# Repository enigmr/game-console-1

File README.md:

## Game Console Project 1

Hobby handheld game console from scratch.

## Top View

## Insides

## Features

- Display: 4.3", 480x272, 16:9, 1200cd/m2, non-touch
- Processor: STM32N657X0
  - Arm Cortex-M55 @ 800 MHz
  - 2D GPU with scaling, rotating, alpha blending, texture mapping
- RAM:
  - 4.2MB on-chip SRAM
  - 32MB off-chip PSRAM
- Storage:
  - 32MB SLC NOR flash
  - Micro SD card slot
- Audio:
  - Stereo DAC with Class-D amplifiers
  - Stereo 1W speakers
- Haptics:
  - Dual vibration motors
- Input:
  - IMU (accelerometer and gyroscope)
  - D-pad
  - A / B / X / Y buttons
  - Start / Select buttons
- Battery:
  - 500mAh Li-Po battery
- Connectivity:
  - USB-C for charging and accessing storage
  - Wi-Fi and Bluetooth via STM32-C6
- Mechanicals:
  - Machined plastic (material TBD)
- Software:
  - Zephyr RTOS
  - Old game console emulators

## Development Tooling

- Schematics and PCB design: KiCad
- 3D modeling: Fusion 360

## Hardware Block Design

TODO

## PCBs

### Top

### Top Bottom

## Schematics 

### Top Sheet

### Audio

### ESP32

### Flash

### Haptics

### IMU

### LCD

### MCU

### Micro SD

### Power

### RAM

### USB Switch

### USB

### Controllers

### Left Board

### Right Board

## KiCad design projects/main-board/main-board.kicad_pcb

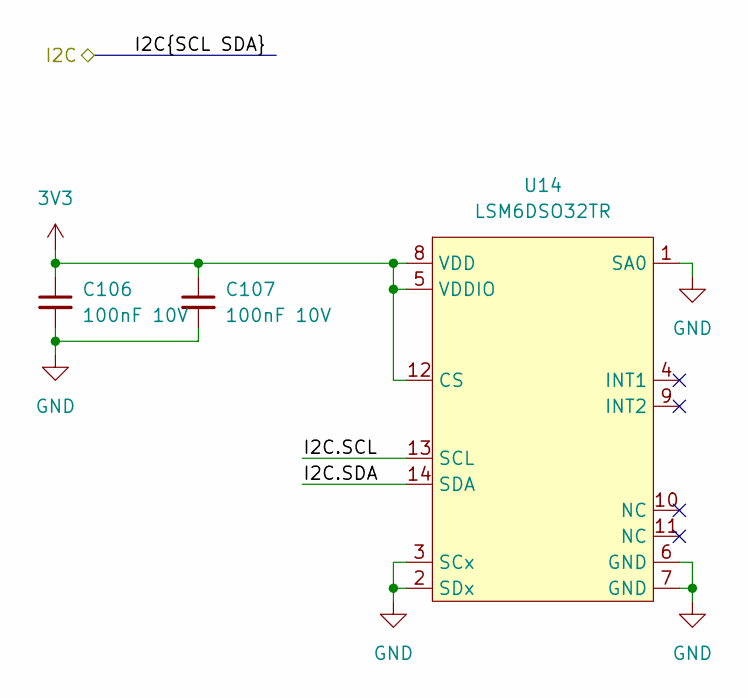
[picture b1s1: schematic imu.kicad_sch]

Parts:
C106, C107: 100nF 10V; C_0402_1005Metric
U14: LSM6DSO32TR

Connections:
3V3: C106.1, C107.1, U14.5 (VDDIO), U14.8 (VDD), U14.12 (CS); also elsewhere on the board
/Audio/I2C.SCL: U14.13 (SCL); also elsewhere on the board
/Audio/I2C.SDA: U14.14 (SDA); also elsewhere on the board
GND: C106.2, C107.2, U14.1 (SA0), U14.2 (SDx), U14.3 (SCx), U14.6 (GND), U14.7 (GND); also elsewhere on the board

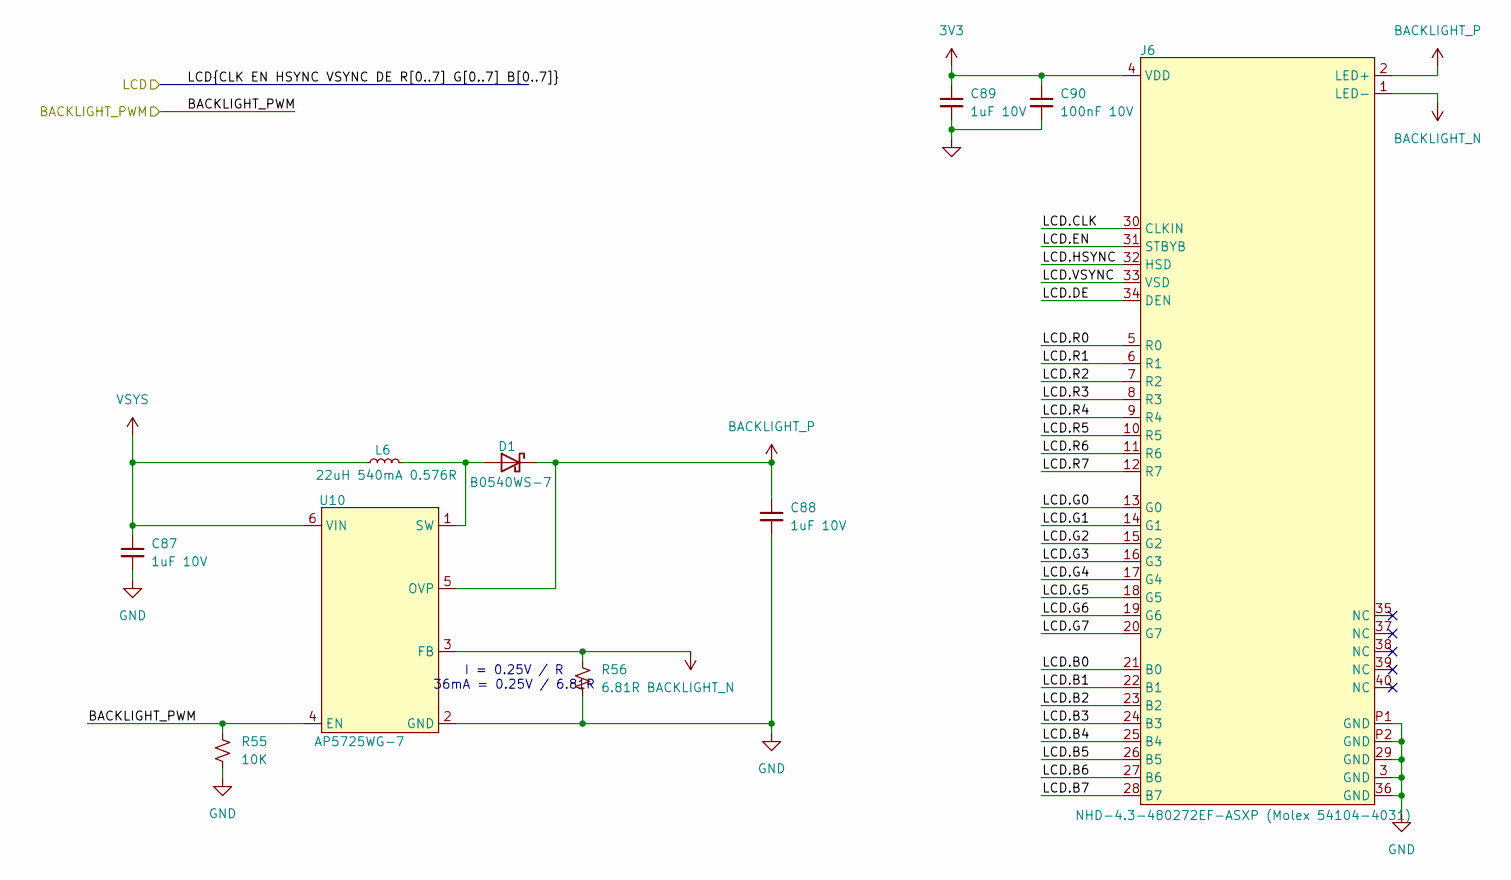
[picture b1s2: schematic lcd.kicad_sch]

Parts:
C87, C88, C89: 1uF 10V; C_0402_1005Metric
C90: 100nF 10V; C_0402_1005Metric
D1: B0540WS-7; SOD323_DIO
J6: NHD-4.3-480272EF-ASXP (Molex 54104-4031); Molex 54104-4031
L6: 22uH 540mA 0.576R; NR4012T220M
R55: 10K; R_0402_1005Metric
R56: 6.81R; R_0402_1005Metric
U10: AP5725WG-7

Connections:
3V3: C89.1, C90.1, J6.4 (VDD); also elsewhere on the board
/LCD/BACKLIGHT_PWM: R55.1, U10.4 (EN); also elsewhere on the board
/LCD/LCD.B0: J6.21 (B0); also elsewhere on the board
/LCD/LCD.B1: J6.22 (B1); also elsewhere on the board
/LCD/LCD.B2: J6.23 (B2); also elsewhere on the board
/LCD/LCD.B3: J6.24 (B3); also elsewhere on the board
/LCD/LCD.B4: J6.25 (B4); also elsewhere on the board
/LCD/LCD.B5: J6.26 (B5); also elsewhere on the board
/LCD/LCD.B6: J6.27 (B6); also elsewhere on the board
/LCD/LCD.B7: J6.28 (B7); also elsewhere on the board
/LCD/LCD.CLK: J6.30 (CLKIN); also elsewhere on the board
/LCD/LCD.DE: J6.34 (DEN); also elsewhere on the board
/LCD/LCD.EN: J6.31 (STBYB); also elsewhere on the board
/LCD/LCD.G0: J6.13 (G0); also elsewhere on the board
/LCD/LCD.G1: J6.14 (G1); also elsewhere on the board
/LCD/LCD.G2: J6.15 (G2); also elsewhere on the board
/LCD/LCD.G3: J6.16 (G3); also elsewhere on the board
/LCD/LCD.G4: J6.17 (G4); also elsewhere on the board
/LCD/LCD.G5: J6.18 (G5); also elsewhere on the board
/LCD/LCD.G6: J6.19 (G6); also elsewhere on the board
/LCD/LCD.G7: J6.20 (G7); also elsewhere on the board
/LCD/LCD.HSYNC: J6.32 (HSD); also elsewhere on the board
/LCD/LCD.R0: J6.5 (R0); also elsewhere on the board
/LCD/LCD.R1: J6.6 (R1); also elsewhere on the board
/LCD/LCD.R2: J6.7 (R2); also elsewhere on the board
/LCD/LCD.R3: J6.8 (R3); also elsewhere on the board
/LCD/LCD.R4: J6.9 (R4); also elsewhere on the board
/LCD/LCD.R5: J6.10 (R5); also elsewhere on the board
/LCD/LCD.R6: J6.11 (R6); also elsewhere on the board
/LCD/LCD.R7: J6.12 (R7); also elsewhere on the board
/LCD/LCD.VSYNC: J6.33 (VSD); also elsewhere on the board
BACKLIGHT_N: J6.1 (LED-), R56.1, U10.3 (FB)
BACKLIGHT_P: C88.1, D1.1 (K), J6.2 (LED+), U10.5 (OVP)
GND: C87.2, C88.2, C89.2, C90.2, J6.3 (GND), J6.29 (GND), J6.36 (GND), J6.P1 (GND), J6.P2 (GND), R55.2, R56.2, U10.2 (GND); also elsewhere on the board
unnamed: D1.2 (A), L6.2, U10.1 (SW)
VSYS: C87.1, L6.1, U10.6 (VIN); also elsewhere on the board

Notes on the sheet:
I = 0.25V / R 36mA = 0.25V / 6.81R

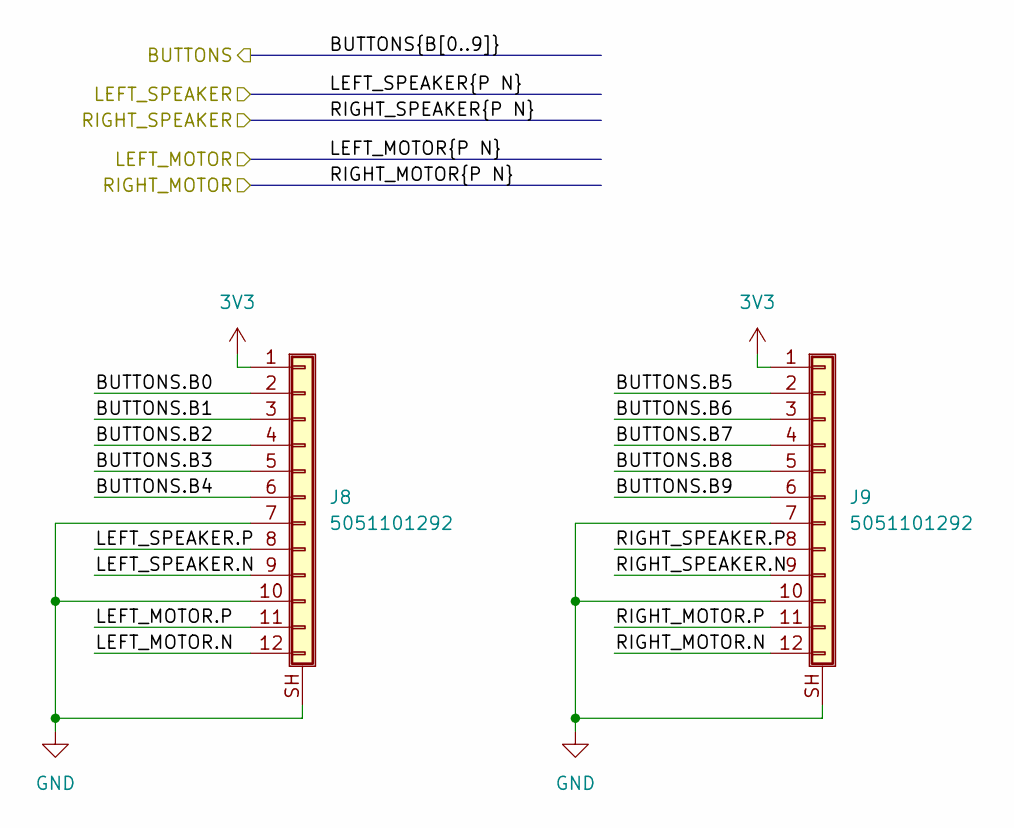
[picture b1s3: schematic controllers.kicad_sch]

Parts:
J8, J9: 5051101292

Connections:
3V3: J8.1, J9.1; also elsewhere on the board
/Audio/LEFT_SPEAKER.N: J8.9; also elsewhere on the board
/Audio/LEFT_SPEAKER.P: J8.8; also elsewhere on the board
/Audio/RIGHT_SPEAKER.N: J9.9; also elsewhere on the board
/Audio/RIGHT_SPEAKER.P: J9.8; also elsewhere on the board
/Controllers/BUTTONS.B0: J8.2; also elsewhere on the board
/Controllers/BUTTONS.B1: J8.3; also elsewhere on the board
/Controllers/BUTTONS.B2: J8.4; also elsewhere on the board
/Controllers/BUTTONS.B3: J8.5; also elsewhere on the board
/Controllers/BUTTONS.B4: J8.6; also elsewhere on the board
/Controllers/BUTTONS.B5: J9.2; also elsewhere on the board
/Controllers/BUTTONS.B6: J9.3; also elsewhere on the board
/Controllers/BUTTONS.B7: J9.4; also elsewhere on the board
/Controllers/BUTTONS.B8: J9.5; also elsewhere on the board
/Controllers/BUTTONS.B9: J9.6; also elsewhere on the board
/Controllers/LEFT_MOTOR.N: J8.12; also elsewhere on the board
/Controllers/LEFT_MOTOR.P: J8.11; also elsewhere on the board
/Controllers/RIGHT_MOTOR.N: J9.12; also elsewhere on the board
/Controllers/RIGHT_MOTOR.P: J9.11
GND: J8.7, J8.10, J8.SH (Shield), J9.7, J9.10, J9.SH (Shield); also elsewhere on the board

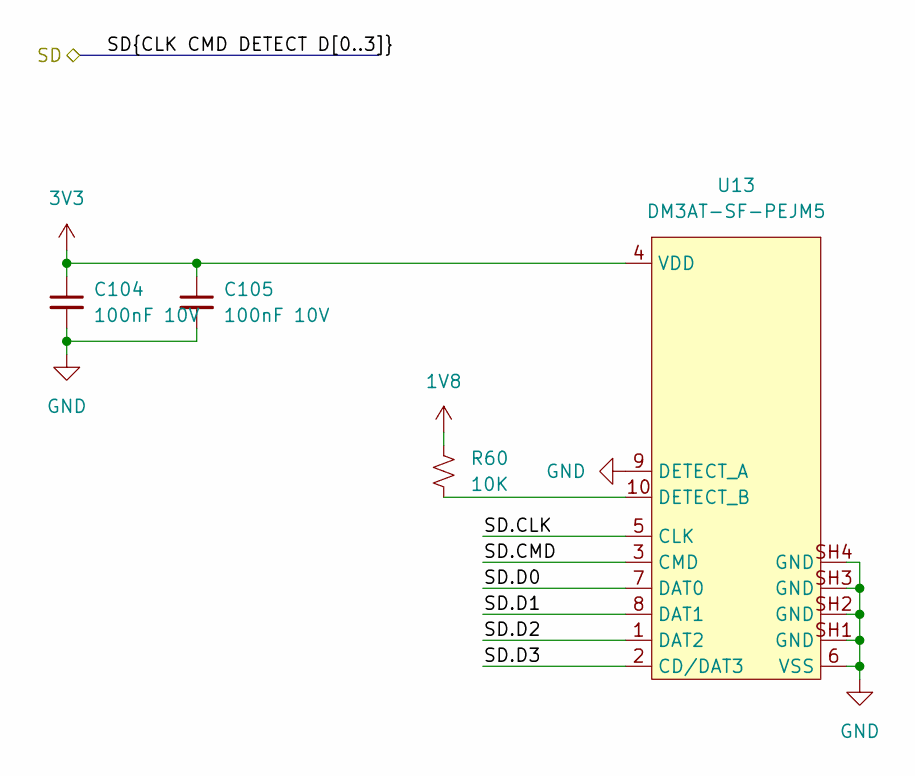
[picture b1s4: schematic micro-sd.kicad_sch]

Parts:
C104, C105: 100nF 10V; C_0402_1005Metric
R60: 10K; R_0402_1005Metric
U13: DM3AT-SF-PEJM5

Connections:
1V8: R60.1; also elsewhere on the board
3V3: C104.1, C105.1, U13.4 (VDD); also elsewhere on the board
/MCU/SD.CLK: U13.5 (CLK); also elsewhere on the board
/MCU/SD.CMD: U13.3 (CMD); also elsewhere on the board
/MCU/SD.D0: U13.7 (DAT0); also elsewhere on the board
/MCU/SD.D1: U13.8 (DAT1); also elsewhere on the board
/MCU/SD.D2: U13.1 (DAT2); also elsewhere on the board
/MCU/SD.D3: U13.2 (CD/DAT3); also elsewhere on the board
GND: C104.2, C105.2, U13.6 (VSS), U13.9 (DETECT_A), U13.SH1 (GND), U13.SH2 (GND), U13.SH3 (GND), U13.SH4 (GND); also elsewhere on the board
unnamed: R60.2, U13.10 (DETECT_B)

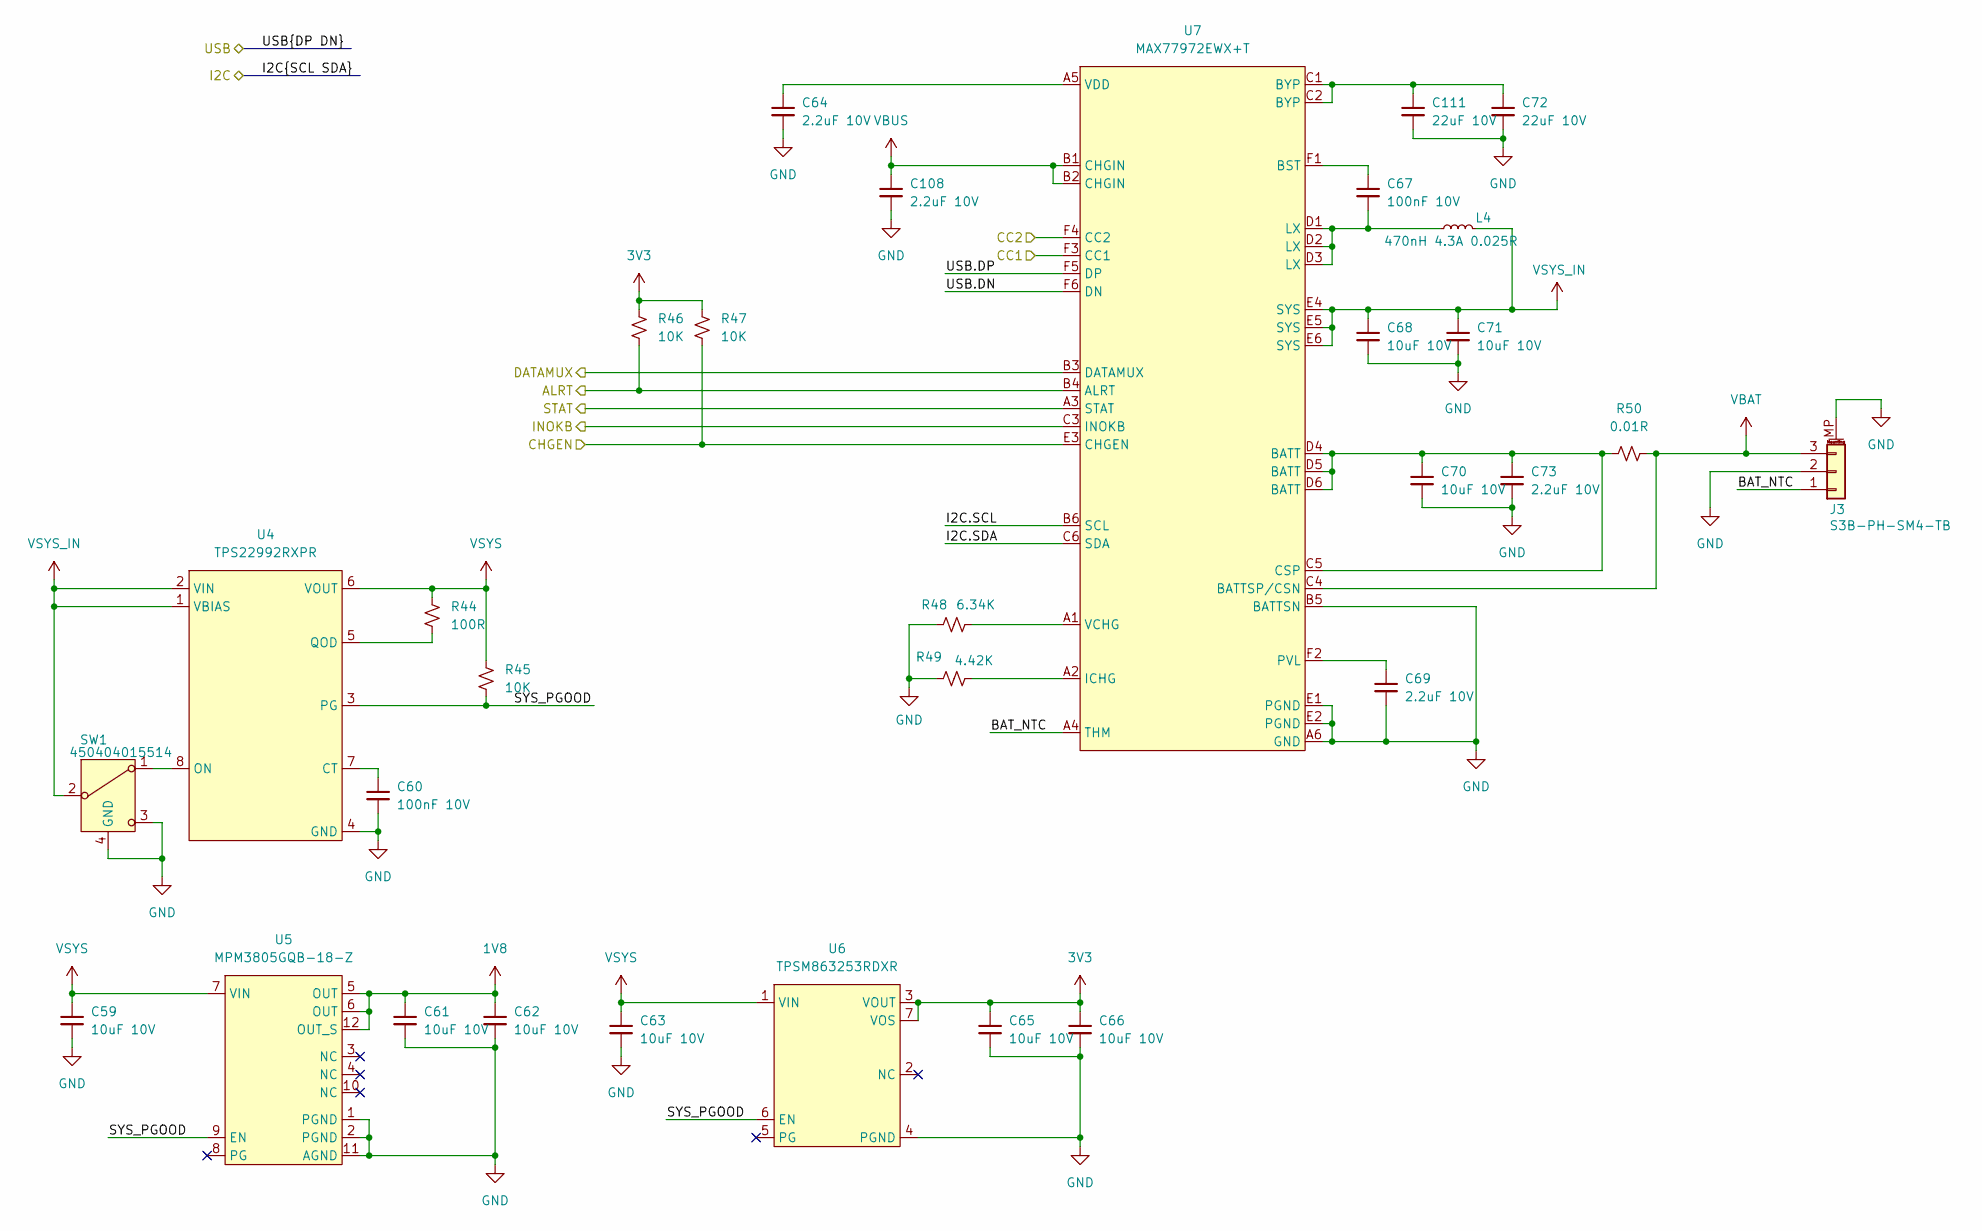
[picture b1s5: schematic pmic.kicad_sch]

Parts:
C59, C61, C62, C63, C65, C66, C68, C70, C71: 10uF 10V; C_0603_1608Metric
C60, C67: 100nF 10V; C_0402_1005Metric
C64, C69, C73, C108: 2.2uF 10V; C_0402_1005Metric
C72, C111: 22uF 10V; C_0603_1608Metric
J3: S3B-PH-SM4-TB
L4: 470nH 4.3A 0.025R; HMLQ25201T-R47MSR
R44: 100R; R_0402_1005Metric
R45, R46, R47: 10K; R_0402_1005Metric
R48: 6.34K; R_0402_1005Metric
R49: 4.42K; R_0402_1005Metric
R50: 0.01R; R_0805_2012Metric
SW1: 450404015514
U4: TPS22992RXPR
U5: MPM3805GQB-18-Z
U6: TPSM863253RDXR
U7: MAX77972EWX+T

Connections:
1V8: C61.1, C62.1, U5.5 (OUT), U5.6 (OUT), U5.12 (OUT_S); also elsewhere on the board
3V3: C65.1, C66.1, R46.1, R47.1, U6.3 (VOUT), U6.7 (VOS); also elsewhere on the board
/MCU/I2C4.SCL: U7.B6 (SCL); also elsewhere on the board
/MCU/I2C4.SDA: U7.C6 (SDA); also elsewhere on the board
/MCU/PMIC_ALERT: R46.2, U7.B4 (ALRT); also elsewhere on the board
/MCU/PMIC_CHARGE_EN: R47.2, U7.E3 (CHGEN); also elsewhere on the board
/MCU/PMIC_INPUT_VALID: U7.C3 (INOKB); also elsewhere on the board
/MCU/PMIC_STATUS: U7.A3 (STAT); also elsewhere on the board
/Power/BAT_NTC: J3.1, U7.A4 (THM)
/Power/DATAMUX: U7.B3 (DATAMUX); also elsewhere on the board
/Power/SYS_PGOOD: R45.2, U4.3 (PG), U5.9 (EN), U6.6 (EN)
/Power/USB.DN: U7.F6 (DN); also elsewhere on the board
/Power/USB.DP: U7.F5 (DP); also elsewhere on the board
/USB/USB_CC1: U7.F3 (CC1); also elsewhere on the board
/USB/USB_CC2: U7.F4 (CC2); also elsewhere on the board
GND: C59.2, C60.2, C61.2, C62.2, C63.2, C64.2, C65.2, C66.2, C68.2, C69.2, C70.2, C71.2, C72.2, C73.2, C108.2, C111.2, J3.2, J3.MP (MountPin), R48.1, R49.1, SW1.3, SW1.4 (GND), U4.4 (GND), U5.1 (PGND), U5.2 (PGND), U5.11 (AGND), U6.4 (PGND), U7.A6 (GND), U7.B5 (BATTSN), U7.E1 (PGND), U7.E2 (PGND); also elsewhere on the board
unnamed: C67.2, L4.1, U7.D1 (LX), U7.D2 (LX), U7.D3 (LX)
unnamed: C72.1, C111.1, U7.C1 (BYP), U7.C2 (BYP)
unnamed: C60.1, U4.7 (CT)
unnamed: SW1.1, U4.8 (ON)
unnamed: R44.2, U4.5 (QOD)
unnamed: C67.1, U7.F1 (BST)
unnamed: C70.1, C73.1, R50.1, U7.C5 (CSP), U7.D4 (BATT), U7.D5 (BATT), U7.D6 (BATT)
unnamed: R49.2, U7.A2 (ICHG)
unnamed: C69.1, U7.F2 (PVL)
unnamed: R48.2, U7.A1 (VCHG)
unnamed: C64.1, U7.A5 (VDD)
VBAT: J3.3, R50.2, U7.C4 (BATTSP/CSN); also elsewhere on the board
VBUS: C108.1, U7.B1 (CHGIN), U7.B2 (CHGIN); also elsewhere on the board
VSYS: C59.1, C63.1, R44.1, R45.1, U4.6 (VOUT), U5.7 (VIN), U6.1 (VIN); also elsewhere on the board
VSYS_IN: C68.1, C71.1, L4.2, SW1.2, U4.1 (VBIAS), U4.2 (VIN), U7.E4 (SYS), U7.E5 (SYS), U7.E6 (SYS)

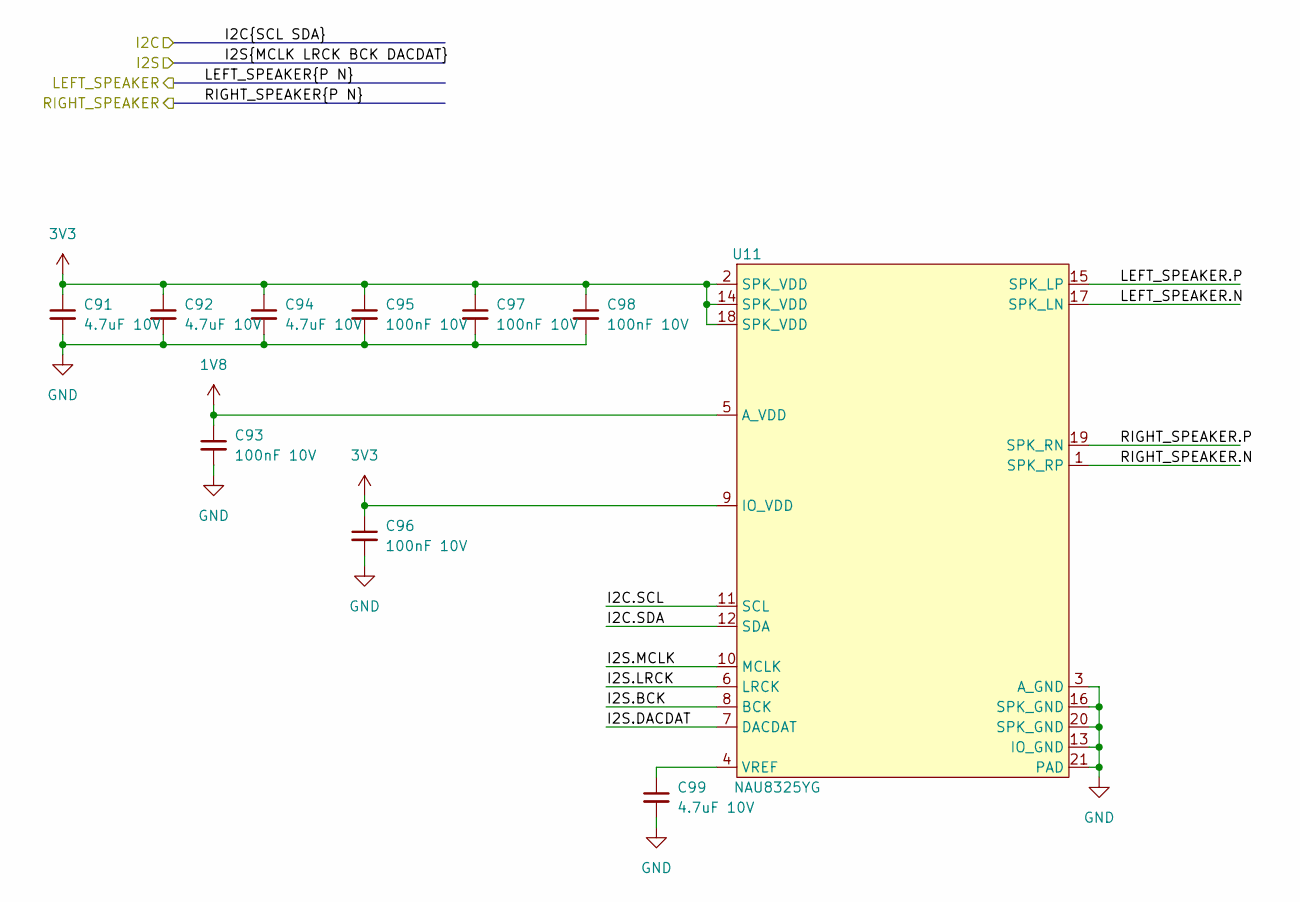
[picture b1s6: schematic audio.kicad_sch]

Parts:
C91, C92, C94, C99: 4.7uF 10V; C_0402_1005Metric
C93, C95, C96, C97, C98: 100nF 10V; C_0402_1005Metric
U11: NAU8325YG

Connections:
1V8: C93.1, U11.5 (A_VDD); also elsewhere on the board
3V3: C91.1, C92.1, C94.1, C95.1, C96.1, C97.1, C98.1, U11.2 (SPK_VDD), U11.9 (IO_VDD), U11.14 (SPK_VDD), U11.18 (SPK_VDD); also elsewhere on the board
/Audio/I2C.SCL: U11.11 (SCL); also elsewhere on the board
/Audio/I2C.SDA: U11.12 (SDA); also elsewhere on the board
/Audio/I2S.BCK: U11.8 (BCK); also elsewhere on the board
/Audio/I2S.DACDAT: U11.7 (DACDAT); also elsewhere on the board
/Audio/I2S.LRCK: U11.6 (LRCK); also elsewhere on the board
/Audio/I2S.MCLK: U11.10 (MCLK); also elsewhere on the board
/Audio/LEFT_SPEAKER.N: U11.17 (SPK_LN); also elsewhere on the board
/Audio/LEFT_SPEAKER.P: U11.15 (SPK_LP); also elsewhere on the board
/Audio/RIGHT_SPEAKER.N: U11.1 (SPK_RP); also elsewhere on the board
/Audio/RIGHT_SPEAKER.P: U11.19 (SPK_RN); also elsewhere on the board
GND: C91.2, C92.2, C93.2, C94.2, C95.2, C96.2, C97.2, C98.2, C99.2, U11.3 (A_GND), U11.13 (IO_GND), U11.16 (SPK_GND), U11.20 (SPK_GND), U11.21 (PAD); also elsewhere on the board
unnamed: C99.1, U11.4 (VREF)

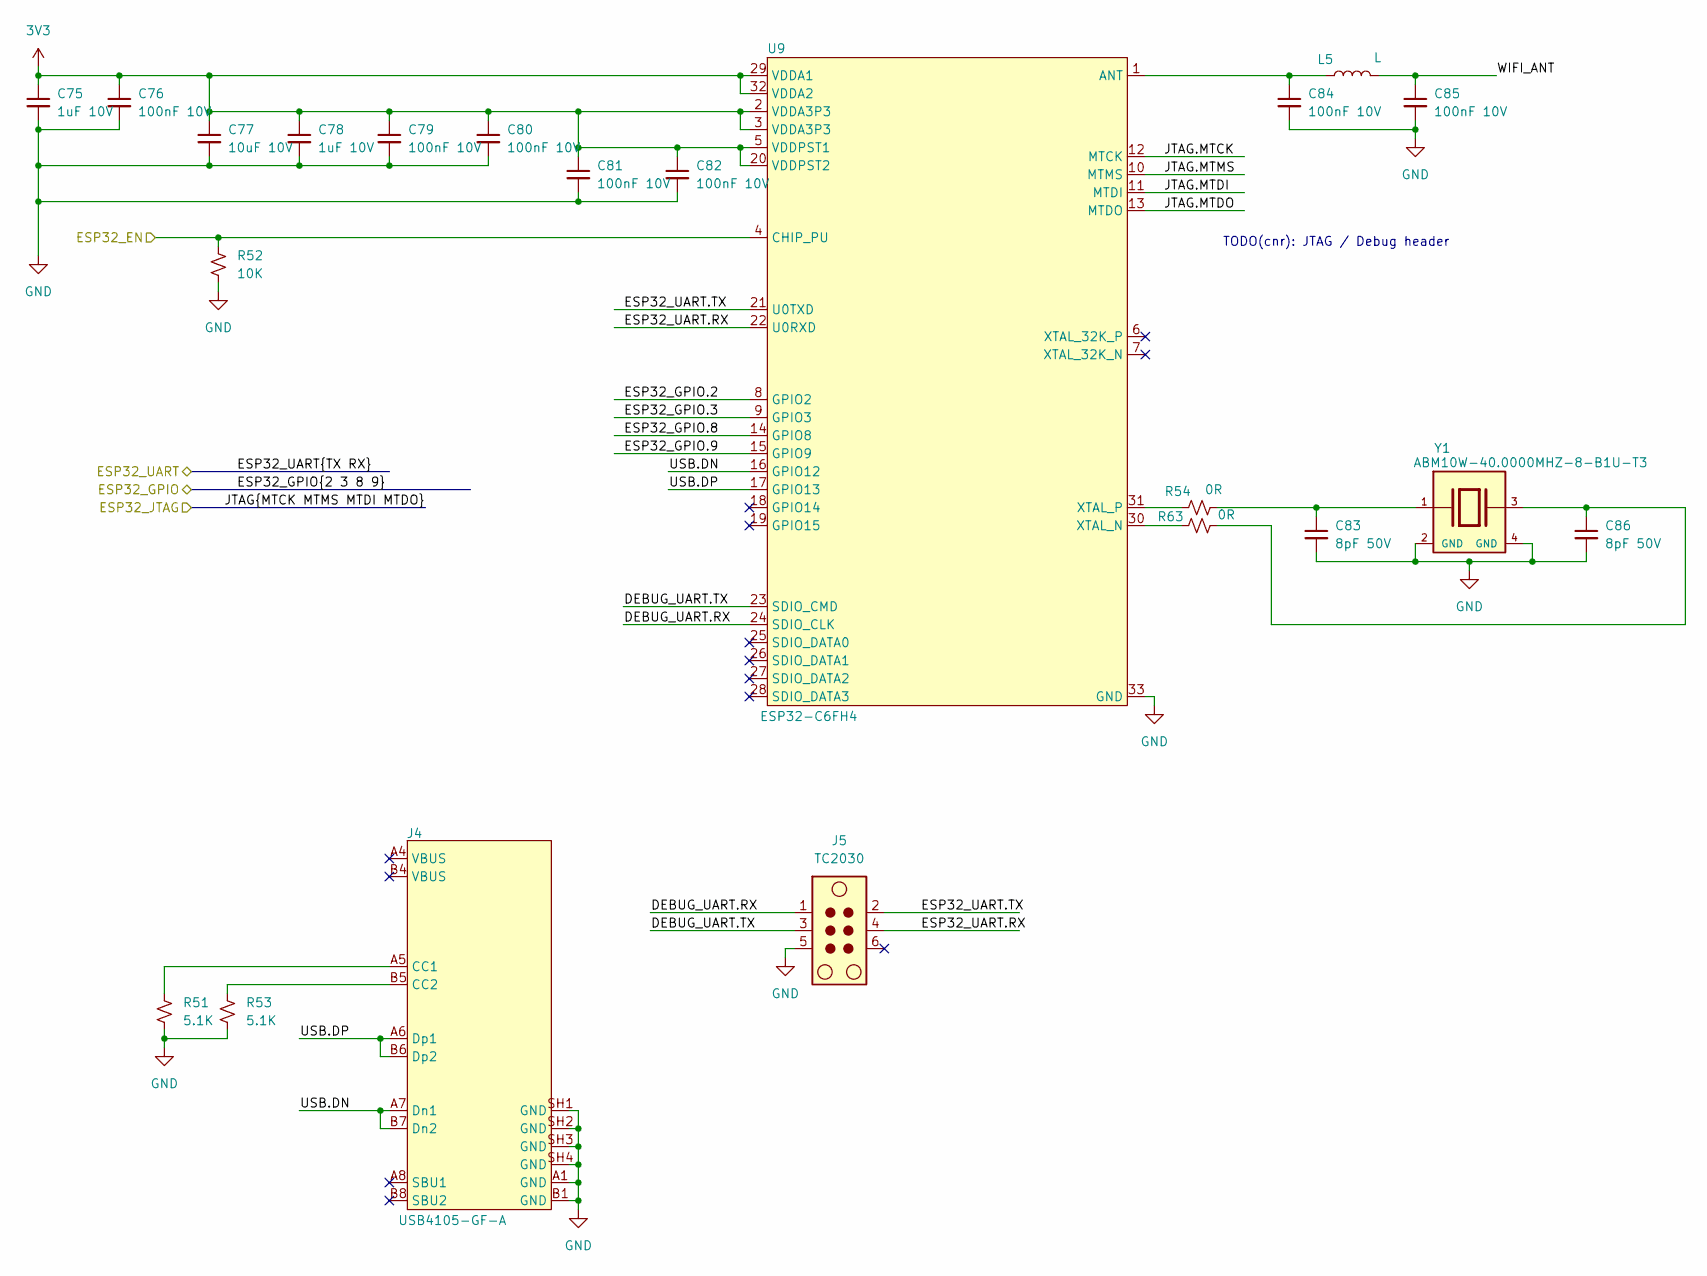
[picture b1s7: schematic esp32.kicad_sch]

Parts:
C75, C78: 1uF 10V; C_0402_1005Metric
C76, C79, C80, C81, C82, C84, C85: 100nF 10V; C_0402_1005Metric
C77: 10uF 10V; C_0603_1608Metric
C83, C86: 8pF 50V; C_0402_1005Metric
J4: USB4105-GF-A
J5: TC2030; Tag-Connect_TC2030-IDC-NL_2x03_P1.27mm_Vertical
L5: L
R51, R53: 5.1K; R_0402_1005Metric
R52: 10K; R_0402_1005Metric
R54, R63: 0R; R_0402_1005Metric
U9: ESP32-C6FH4
Y1: ABM10W-40.0000MHZ-8-B1U-T3; XTAL_ABM10W-40.0000MHZ-8-B1U-T3

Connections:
3V3: C75.1, C76.1, C77.1, C78.1, C79.1, C80.1, C81.1, C82.1, U9.2 (VDDA3P3), U9.3 (VDDA3P3), U9.5 (VDDPST1), U9.20 (VDDPST2), U9.29 (VDDA1), U9.32 (VDDA2); also elsewhere on the board
/ESP32/DEBUG_UART.RX: J5.1, U9.24 (SDIO_CLK)
/ESP32/DEBUG_UART.TX: J5.3, U9.23 (SDIO_CMD)
/ESP32/ESP32_GPIO.2: U9.8 (GPIO2); also elsewhere on the board
/ESP32/ESP32_GPIO.3: U9.9 (GPIO3); also elsewhere on the board
/ESP32/ESP32_GPIO.8: U9.14 (GPIO8); also elsewhere on the board
/ESP32/ESP32_GPIO.9: U9.15 (GPIO9); also elsewhere on the board
/ESP32/ESP32_UART.RX: J5.4, U9.22 (U0RXD); also elsewhere on the board
/ESP32/ESP32_UART.TX: J5.2, U9.21 (U0TXD); also elsewhere on the board
/ESP32/JTAG.MTCK: U9.12 (MTCK)
/ESP32/JTAG.MTDI: U9.11 (MTDI)
/ESP32/JTAG.MTDO: U9.13 (MTDO)
/ESP32/JTAG.MTMS: U9.10 (MTMS)
/ESP32/USB.DN: J4.A7 (Dn1), J4.B7 (Dn2), U9.16 (GPIO12)
/ESP32/USB.DP: J4.A6 (Dp1), J4.B6 (Dp2), U9.17 (GPIO13)
/ESP32/WIFI_ANT: C85.1, L5.2
/MCU/ESP32_EN: R52.1, U9.4 (CHIP_PU); also elsewhere on the board
GND: C75.2, C76.2, C77.2, C78.2, C79.2, C80.2, C81.2, C82.2, C83.2, C84.2, C85.2, C86.2, J4.A1 (GND), J4.B1 (GND), J4.SH1 (GND), J4.SH2 (GND), J4.SH3 (GND), J4.SH4 (GND), J5.5, R51.2, R52.2, R53.2, U9.33 (GND), Y1.2 (GND), Y1.4 (GND); also elsewhere on the board
unnamed: C83.1, R54.2, Y1.1
unnamed: C86.1, R63.2, Y1.3
unnamed: J4.A5 (CC1), R51.1
unnamed: J4.B5 (CC2), R53.1
unnamed: C84.1, L5.1, U9.1 (ANT)
unnamed: R63.1, U9.30 (XTAL_N)
unnamed: R54.1, U9.31 (XTAL_P)

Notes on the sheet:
TODO(cnr): JTAG / Debug header

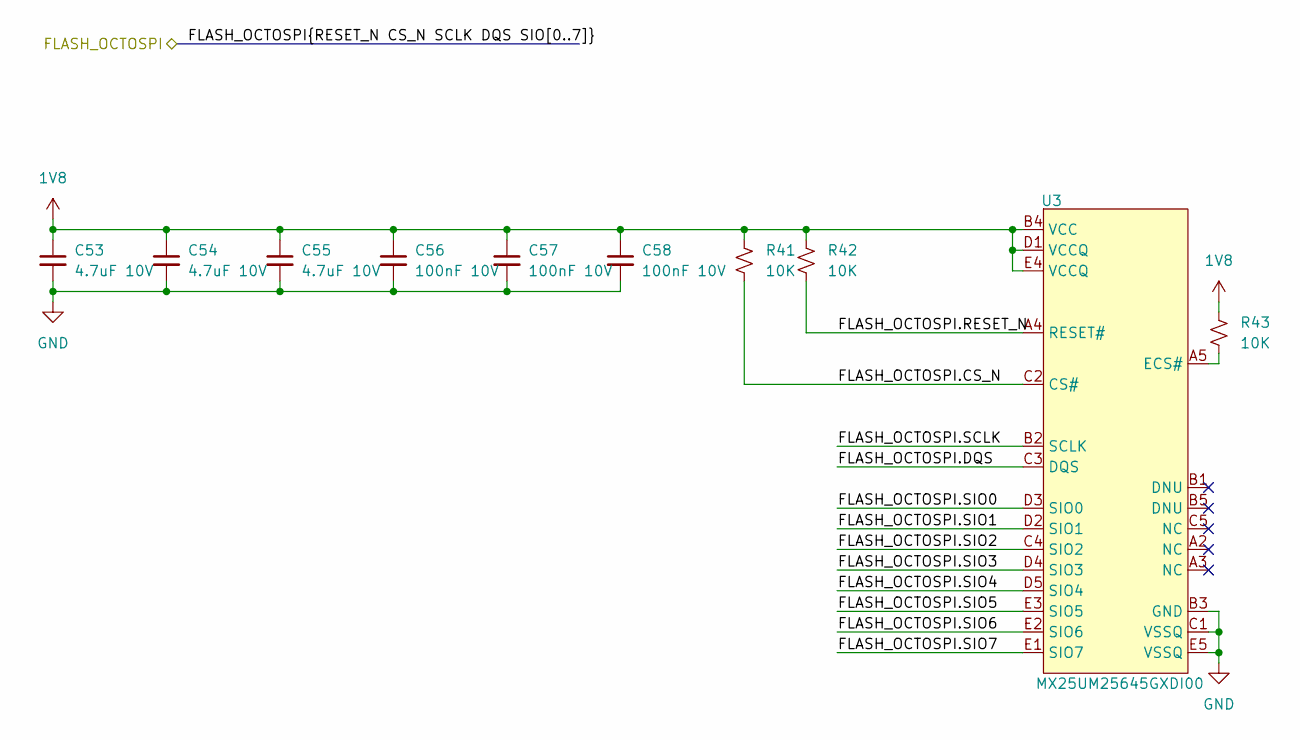
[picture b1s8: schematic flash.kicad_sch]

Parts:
C53, C54, C55: 4.7uF 10V; C_0402_1005Metric
C56, C57, C58: 100nF 10V; C_0402_1005Metric
R41, R42, R43: 10K; R_0402_1005Metric
U3: MX25UM25645GXDI00

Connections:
1V8: C53.1, C54.1, C55.1, C56.1, C57.1, C58.1, R41.1, R42.1, R43.1, U3.B4 (VCC), U3.D1 (VCCQ), U3.E4 (VCCQ); also elsewhere on the board
/Flash/FLASH_OCTOSPI.CS_N: R41.2, U3.C2 (CS#); also elsewhere on the board
/Flash/FLASH_OCTOSPI.DQS: U3.C3 (DQS); also elsewhere on the board
/Flash/FLASH_OCTOSPI.RESET_N: R42.2, U3.A4 (RESET#); also elsewhere on the board
/Flash/FLASH_OCTOSPI.SCLK: U3.B2 (SCLK); also elsewhere on the board
/Flash/FLASH_OCTOSPI.SIO0: U3.D3 (SIO0); also elsewhere on the board
/Flash/FLASH_OCTOSPI.SIO1: U3.D2 (SIO1); also elsewhere on the board
/Flash/FLASH_OCTOSPI.SIO2: U3.C4 (SIO2); also elsewhere on the board
/Flash/FLASH_OCTOSPI.SIO3: U3.D4 (SIO3); also elsewhere on the board
/Flash/FLASH_OCTOSPI.SIO4: U3.D5 (SIO4); also elsewhere on the board
/Flash/FLASH_OCTOSPI.SIO5: U3.E3 (SIO5); also elsewhere on the board
/Flash/FLASH_OCTOSPI.SIO6: U3.E2 (SIO6); also elsewhere on the board
/Flash/FLASH_OCTOSPI.SIO7: U3.E1 (SIO7); also elsewhere on the board
GND: C53.2, C54.2, C55.2, C56.2, C57.2, C58.2, U3.B3 (GND), U3.C1 (VSSQ), U3.E5 (VSSQ); also elsewhere on the board
unnamed: R43.2, U3.A5 (ECS#)
